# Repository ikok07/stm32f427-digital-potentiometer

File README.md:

# STM32F427 Digital Potentiometer

A bare-metal firmware for the **STM32F427ZGTx** microcontroller that emulates a real analog potentiometer using a rotary encoder and a DAC output. Encoder pulses are counted in hardware via TIM2 in encoder mode, and the resulting 12-bit value is converted to an analog voltage on **PA4** (DAC1 Channel 1), making the output electrically indistinguishable from a wiper-voltage of a physical potentiometer.

---

## Overview

```
Rotary Encoder ──► TIM2 (encoder mode) ──► Event Manager ──► DAC1 CH1 ──► Analog Voltage (PA4)
                         │
                    RTC Backup Register  (value persisted across resets)
```

Every detent of the rotary encoder increments or decrements a 12-bit counter (0 – 4096). The counter value is immediately written to DAC1 Channel 1, producing a proportional analog output voltage between **0 V** and **V_REF** (3.3 V). The current position is stored in the RTC backup register **DR0** so the last-known position survives a power cycle or soft reset.

Pressing the encoder's push-button resets the position back to **0**.

---

## Features

| Feature           | Details                                                     |
|-------------------|-------------------------------------------------------------|
| Encoder interface | TIM2 hardware encoder mode (both edges, noise filter `0xF`) |
| DAC resolution    | 12-bit right-aligned (0 – 4095 → 0 – V_REF)                 |
| Value persistence | RTC backup register DR0 (survives resets / power loss)      |
| Encoder reset     | EXTI2 interrupt on PA2 (encoder push-button)                |
| Debug logging     | USART1 TX @ 9600 8N1 (printf redirect)                      |
| Error indication  | Error LED on PC0, error messages via USART                  |
| Build system      | CMake + arm-none-eabi-gcc                                   |
| Debug probe       | ST-LINK v2 / OpenOCD                                        |

---

## Hardware

### Pin Mapping

| Pin   | Peripheral | Function                                     |
|-------|------------|----------------------------------------------|
| PA0   | TIM2 CH1   | Encoder channel A (TI1)                      |
| PA1   | TIM2 CH2   | Encoder channel B (TI2)                      |
| PA2   | EXTI2      | Encoder push-button (reset position to 0)    |
| PA4   | DAC1 CH1   | Analog output (emulated potentiometer wiper) |
| PA9   | USART1 TX  | Debug serial output                          |
| PA10  | USART1 RX  | Debug serial input                           |
| PC0   | GPIO OUT   | Error LED                                    |

> The DAC output on **PA4** can be fed directly into an audio amplifier, analog control input, or any circuit that expects a variable wiper voltage.

---

## Software Architecture

### Module Breakdown

```
src/
├── main.c              – Peripheral initialisation and superloop
├── encoder.c           – TIM2 encoder setup, IC capture ISR, EXTI reset ISR
├── dac.c               – DAC1 channel 1 initialisation
├── event_manager.c     – Translates encoder value to a DAC output value
├── error.c             – Error LED + USART error reporting
├── stm32fxxx_it.c      – SysTick, TIM2 and EXTI2 interrupt vectors
└── msp/
    ├── tim_msp.c       – GPIO & NVIC low-level init for TIM2
    ├── dac_msp.c       – GPIO low-level init for DAC1 (PA4 analog)
    └── usart_msp.c     – GPIO low-level init for USART1
```

**Encoder flow:**

1. `ENC_Setup()` — initialises TIM2 in encoder mode and restores the last position from the RTC backup register.
2. `HAL_TIM_IC_CaptureCallback()` — fires on every encoder edge; computes direction-aware delta, clamps value to `[0, 4096]`, persists to backup register, then calls `EM_HandleNewEncValue()`.
3. `EM_HandleNewEncValue()` — writes the new 12-bit value to `DAC1 CH1` using `HAL_DAC_SetValue()`.
4. `HAL_GPIO_EXTI_Callback()` — resets position to 0 when the push-button is pressed (PA2 rising edge).

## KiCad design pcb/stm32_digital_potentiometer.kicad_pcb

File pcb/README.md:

# STM32 Digital Potentiomer Module

### Description:

The main purpose of this module is to replace the need to use a physical multi turn potentiometer in places where they
are frequently used and therefore easly broken. Instead with the help of the digital potentiometer you can use an
encoder which is far more affordable.

### How to use

1. Connect the rotary encoder to the "ENC" connector
2. Connect the "POT" connector to the required potentiometer output that you want to emulate
3. Connect "POWER" connector
4. The "POWER" LED will light up and the module will start converting the digital signals from the encoder into analog ones

### Important information

1. The module is designed to handle <strong>MAX</strong> voltage of <strong>15V</strong>
2. If an error occurs, the "ERROR" LED will light up and the module will restart itself after 1 second
3. In order to debug or update the firmware you should connect the "SWD" and "USART" connectors to a PC with ST-Link Debugger

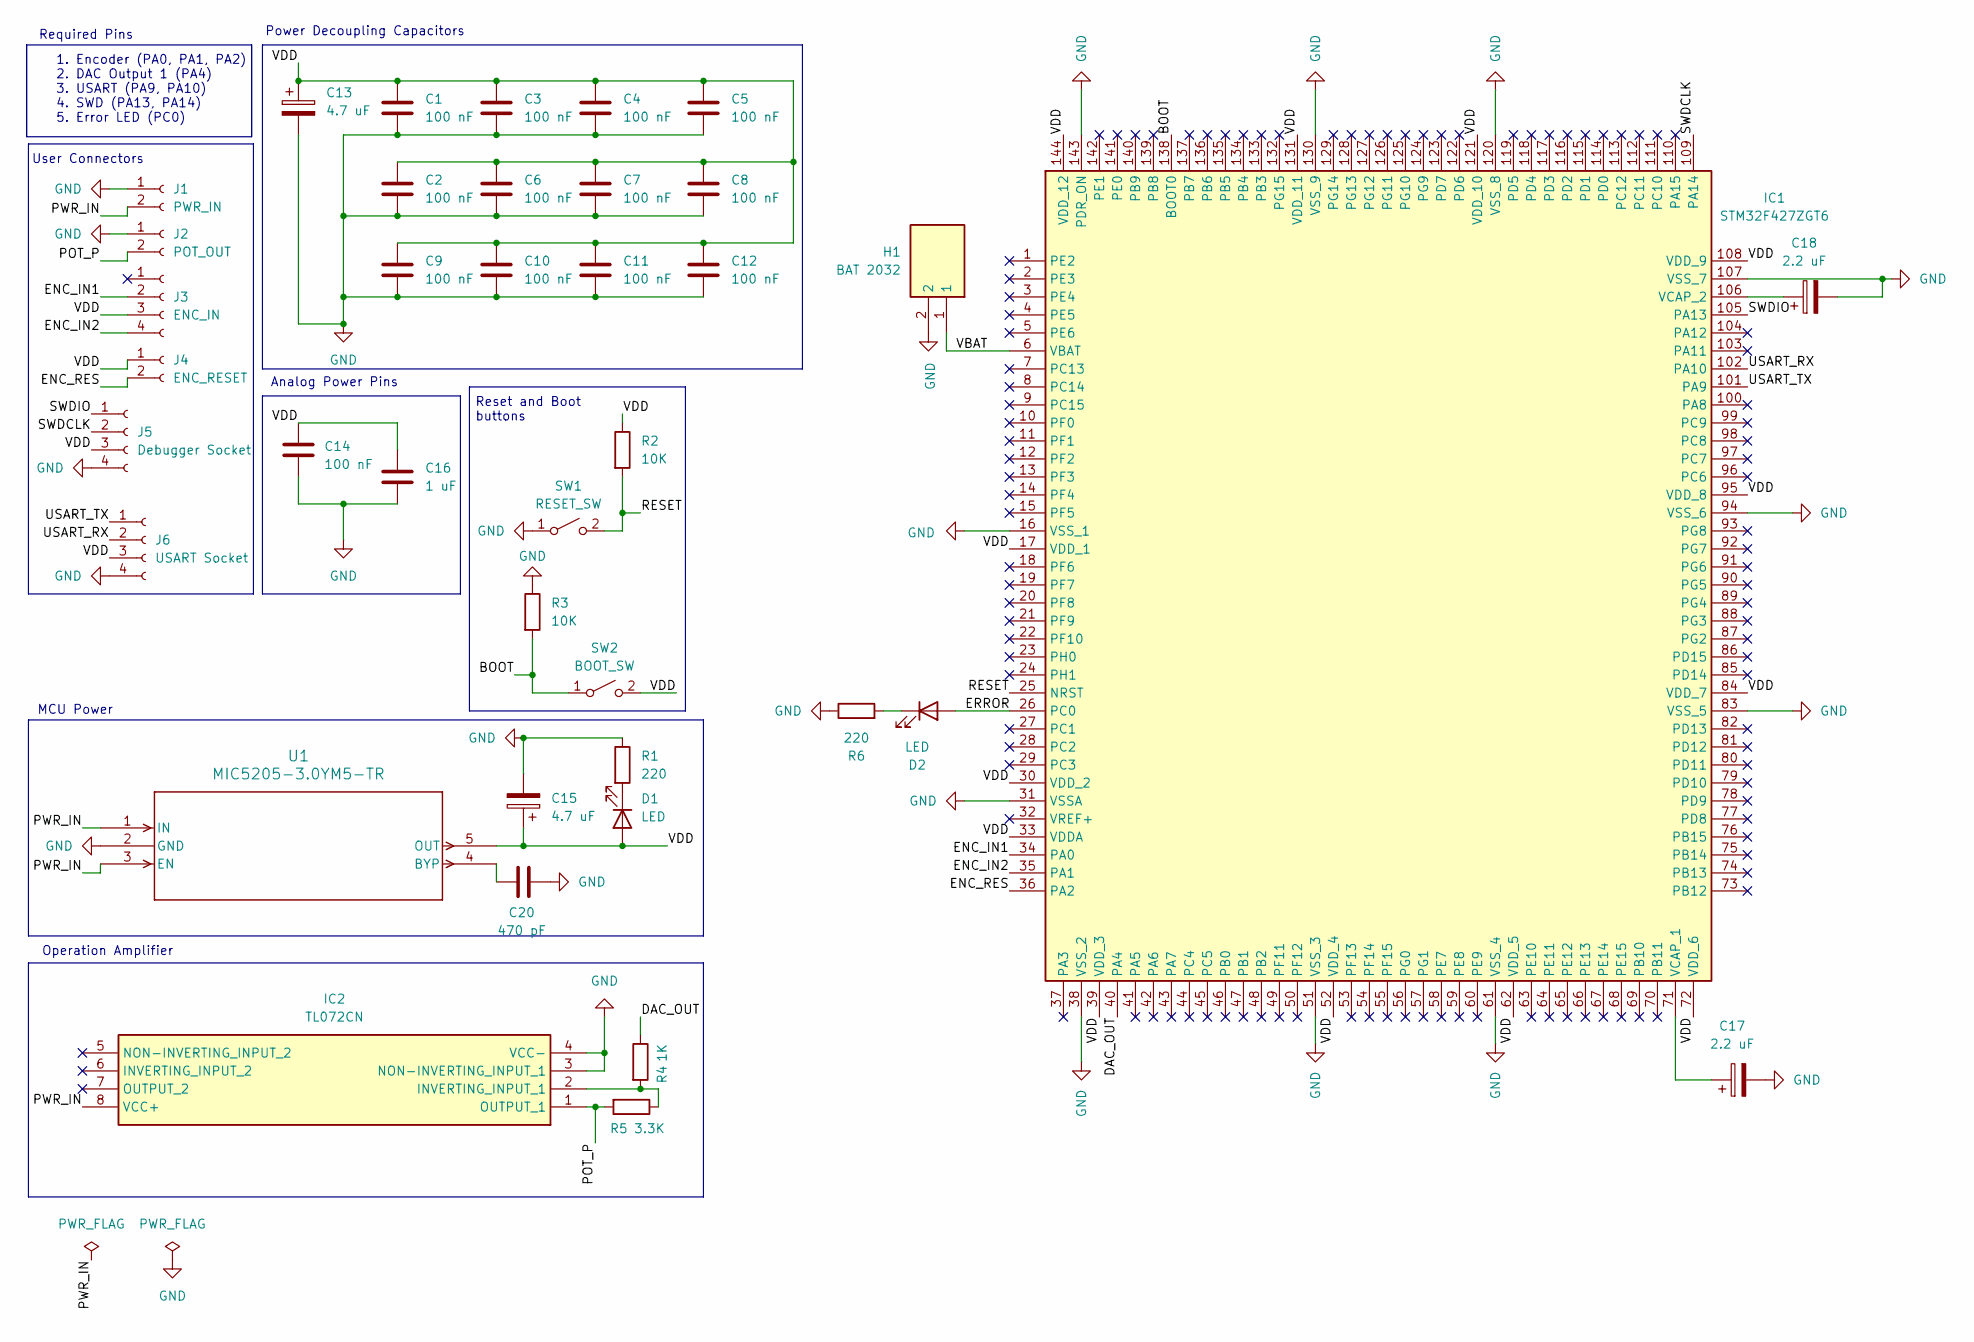
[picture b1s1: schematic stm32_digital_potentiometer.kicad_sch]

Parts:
C1, C2, C3, C4, C5, C6, C7, C8, C9, C10, C11, C12, C14: 100 nF; C_Disc_D3.0mm_W1.6mm_P2.50mm
C13, C15: 4.7 uF; C_Radial_D5.0mm_H11.0mm_P2.00mm
C16: 1 uF; C_Disc_D3.0mm_W1.6mm_P2.50mm
C17, C18: 2.2 uF; C_Radial_D5.0mm_H11.0mm_P2.00mm
C20: 470 pF; C_Disc_D5.0mm_W2.5mm_P5.00mm
D1, D2: LED; LED_D3.0mm
H1: BAT 2032; BATHLD011THM; Mouser Part Number 712-BAT-HLD-011-THM
IC1: STM32F427ZGT6; QFP50P2200X2200X160-144N; Mouser Part Number 511-STM32F427ZGT6
IC2: TL072CN; DIP-8_W10.16mm_LongPads; Manufacturer_Part_Number TL072CN; Mouser Part Number 511-TL072CN
J1: PWR_IN; PinSocket_1x02_P2.00mm_Vertical
J2: POT_OUT; PinSocket_1x02_P2.00mm_Vertical
J3: ENC_IN; PinSocket_1x04_P2.00mm_Vertical
J4: ENC_RESET; PinSocket_1x02_P2.00mm_Vertical
J5: Debugger Socket; PinSocket_1x04_P2.00mm_Vertical
J6: USART Socket; PinSocket_1x04_P2.00mm_Vertical
R1, R6: 220; R_Axial_DIN0414_L11.9mm_D4.5mm_P5.08mm_Vertical
R2, R3: 10K; R_Axial_DIN0414_L11.9mm_D4.5mm_P5.08mm_Vertical
R4: 1K; R_Axial_DIN0414_L11.9mm_D4.5mm_P5.08mm_Vertical
R5: 3.3K; R_Axial_DIN0414_L11.9mm_D4.5mm_P5.08mm_Vertical
SW1: RESET_SW; SW_SPST_PTS647_Sx50
SW2: BOOT_SW; SW_SPST_PTS647_Sx50
U1: MIC5205-3.0YM5-TR; MIC5205-3.0

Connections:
/BOOT: IC1.138 (BOOT0), R3.2, SW2.1 (A)
/DAC_OUT: IC1.40 (PA4), R4.1
/ENC_IN1: IC1.34 (PA0), J3.2
/ENC_IN2: IC1.35 (PA1), J3.4
/ENC_RES: IC1.36 (PA2), J4.2
/ERROR: D2.2 (A), IC1.26 (PC0)
/POT_P: IC2.1 (OUTPUT_1), J2.2, R5.2
/PWR_IN: IC2.8 (VCC+), J1.2, U1.1 (IN), U1.3 (EN)
/RESET: IC1.25 (NRST), R2.2, SW1.2 (B)
/SWDCLK: IC1.109 (PA14), J5.2
/SWDIO: IC1.105 (PA13), J5.1
/USART_RX: IC1.102 (PA10), J6.2
/USART_TX: IC1.101 (PA9), J6.1
/VBAT: H1.1, IC1.6 (VBAT)
/VDD: C1.1, C2.1, C3.1, C4.1, C5.1, C6.1, C7.1, C8.1, C9.1, C10.1, C11.1, C12.1, C13.1, C14.1, C15.1, C16.1, D1.2 (A), IC1.17 (VDD_1), IC1.30 (VDD_2), IC1.33 (VDDA), IC1.39 (VDD_3), IC1.52 (VDD_4), IC1.62 (VDD_5), IC1.72 (VDD_6), IC1.84 (VDD_7), IC1.95 (VDD_8), IC1.108 (VDD_9), IC1.121 (VDD_10), IC1.131 (VDD_11), IC1.144 (VDD_12), J3.3, J4.1, J5.3, J6.3, R2.1, SW2.2 (B), U1.5 (OUT)
GND: C1.2, C2.2, C3.2, C4.2, C5.2, C6.2, C7.2, C8.2, C9.2, C10.2, C11.2, C12.2, C13.2, C14.2, C15.2, C16.2, C17.2, C18.2, C20.2, H1.2, IC1.16 (VSS_1), IC1.31 (VSSA), IC1.38 (VSS_2), IC1.51 (VSS_3), IC1.61 (VSS_4), IC1.83 (VSS_5), IC1.94 (VSS_6), IC1.107 (VSS_7), IC1.120 (VSS_8), IC1.130 (VSS_9), IC1.143 (PDR_ON), IC2.3 (NON-INVERTING_INPUT_1), IC2.4 (VCC-), J1.1, J2.1, J5.4, J6.4, R1.1, R3.1, R6.1, SW1.1 (A), U1.2 (GND)
unnamed: D1.1 (K), R1.2
unnamed: D2.1 (K), R6.2
unnamed: C17.1, IC1.71 (VCAP_1)
unnamed: C18.1, IC1.106 (VCAP_2)
unnamed: IC2.2 (INVERTING_INPUT_1), R4.2, R5.1
unnamed: C20.1, U1.4 (BYP)

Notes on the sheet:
Analog Power Pins
MCU Power
1. Encoder (PA0, PA1, PA2) 2. DAC Output 1 (PA4) 3. USART (PA9, PA10) 4. SWD (PA13, PA14) 5. Error LED (PC0)
Power Decoupling Capacitors
Required Pins
Operation Amplifier
User Connectors
Reset and Boot buttons

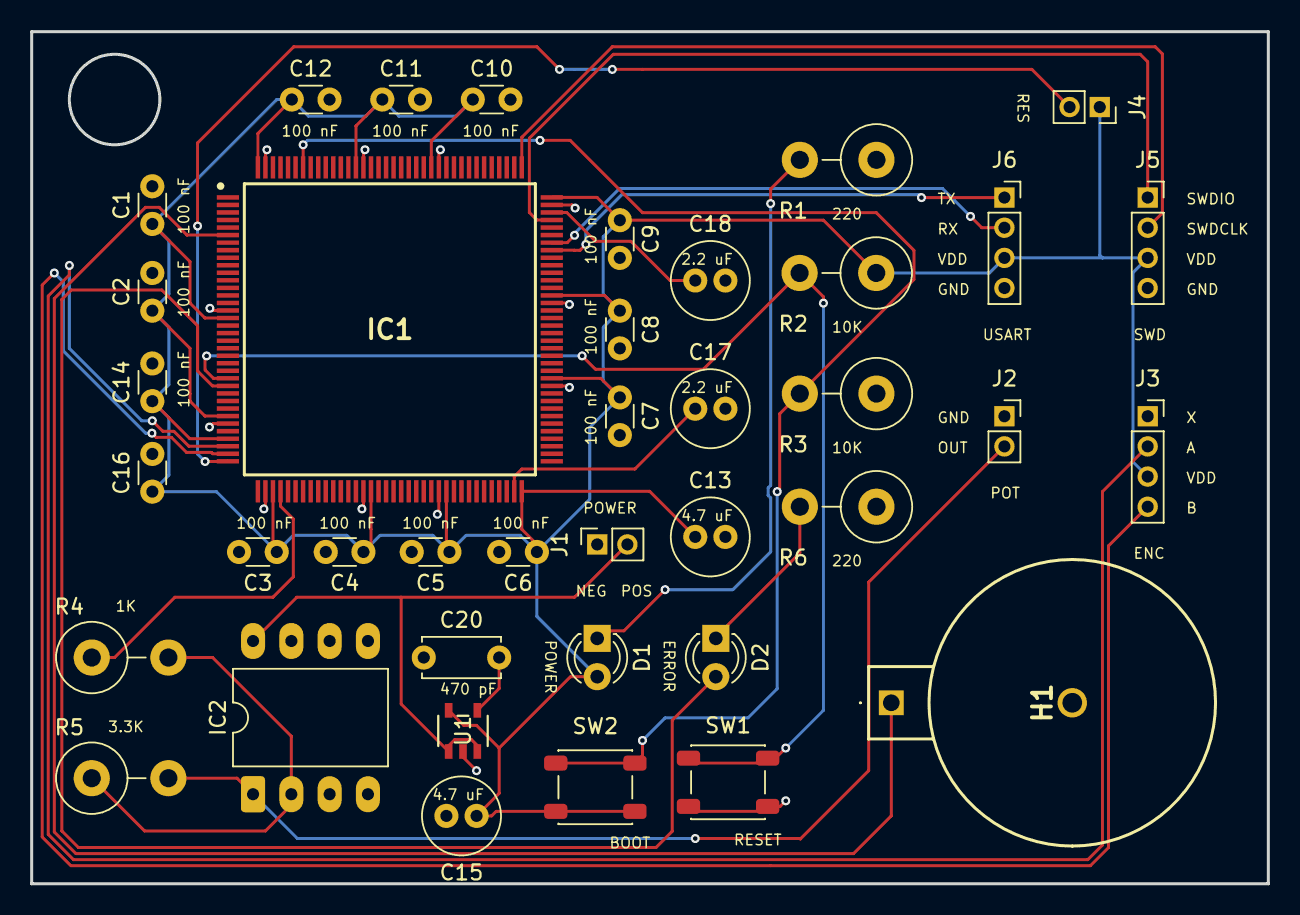
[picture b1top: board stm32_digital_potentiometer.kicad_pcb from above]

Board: 2 copper layers, 82.0 x 56.5 mm, 39 parts (0 on the bottom side), 22 nets.

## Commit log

2026-03-28 refactor: rename setup functions for DAC and encoder to follow naming conventions
2026-03-28 add pcb image
2026-03-28 add pcb image to README
2026-03-28 update README: remove table of contents section
2026-04-05 fix error module not initialized and some RCC clocks not being activated
